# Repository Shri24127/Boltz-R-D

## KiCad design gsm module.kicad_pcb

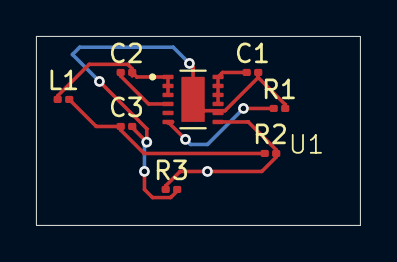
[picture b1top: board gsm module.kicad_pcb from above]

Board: 2 copper layers, 18.0 x 10.5 mm, 8 parts (0 on the bottom side), 7 nets.

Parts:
C1, C2, C3: C; C_0201_0603Metric
L1: L; L_0201_0603Metric
R1, R2, R3: R; R_0201_0603Metric
U1: LMR51450SDRRR; lmr

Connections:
+7.6V: C1.1, U1.9 (EN), U1.10 (VIN), U1.11 (VIN), U1.12 (VIN)
GND: C1.2, C3.2, R1.2, R3.2, U1.8 (AGND), U1.13 (PGND)
unnamed: C2.2, L1.1, U1.1 (SW), U1.2 (SW), U1.3 (SW)
unnamed: C3.1, L1.2, R2.1
unnamed: C2.1, U1.4 (BOOT)
unnamed: R2.2, R3.1, U1.7 (FB)
unnamed: R1.1, U1.6 (RT)
